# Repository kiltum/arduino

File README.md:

# Arduino shield for automation purposes

ATTN: This is picture of very old board. I havent new pictures

What this shield can do?
- Work with any Arduino Nano
- Work from 15-30 AC/DC. 
- Have 4x220v sensor
- Have 4x8A switch relay
- Have 0-10V output
- Have two RS-485
- 3 PT1000/pulled down analog input

## Pin-out for auduio

- D2,D3,D4 - TX,RX and RE/DE of 485
- D11, D12, D13 - for second 485
- D5 - PWM output for 0-10V
- D6 - PWM output for second 0-10V
- D7-D10 - control for switch relay 1-4
- A4,A5,A6,A7 - pulled down input for PT1000
- A0-A3 - sensors input

## Pin-out for board

Take board like on picture

### Top. Left-to-right

- 1 - power in POSITIVE
- 2 - GND
- 3 - RS485B
- 4 - RS485A
- 5 - RS485B2
- 7 - RS485A2
- 6 - GND
- 8 - 5V
- 9 - A4

separator

- 10 - A5
- 11 - A6 
- 12 - A7
- 13 - 0-10V output 2
- 14 - 0-10V output 1
- 15 - GND
- 16 - R4 closed
- 17 - R4 open	
- 18 - R4 ground

### Bottom, left to right

- 1 - Sensor 1 220V / 24V Positive
- 2 - Sensor 1
- 3 - Sensor 2 220v / 24V Positive
- 4 - Sensor 2
- 5 - Sensor 3 220v / 24V Positive
- 6 - Sensor 3
- 7 - Sensor 4 220v / 24V Positive
- 8 - Sensor 4
- 9 - not connected

separator

- 10 - R1 ground
- 11 - R1 closed
- 12 - R1 open
- 13 - R2 ground 
- 14 - R2 closed
- 15 - R2 open
- 16 - R3 ground
- 17 - R3 close
- 18 - R3 open

## License

Do what you want. I do not rely for anything you do.

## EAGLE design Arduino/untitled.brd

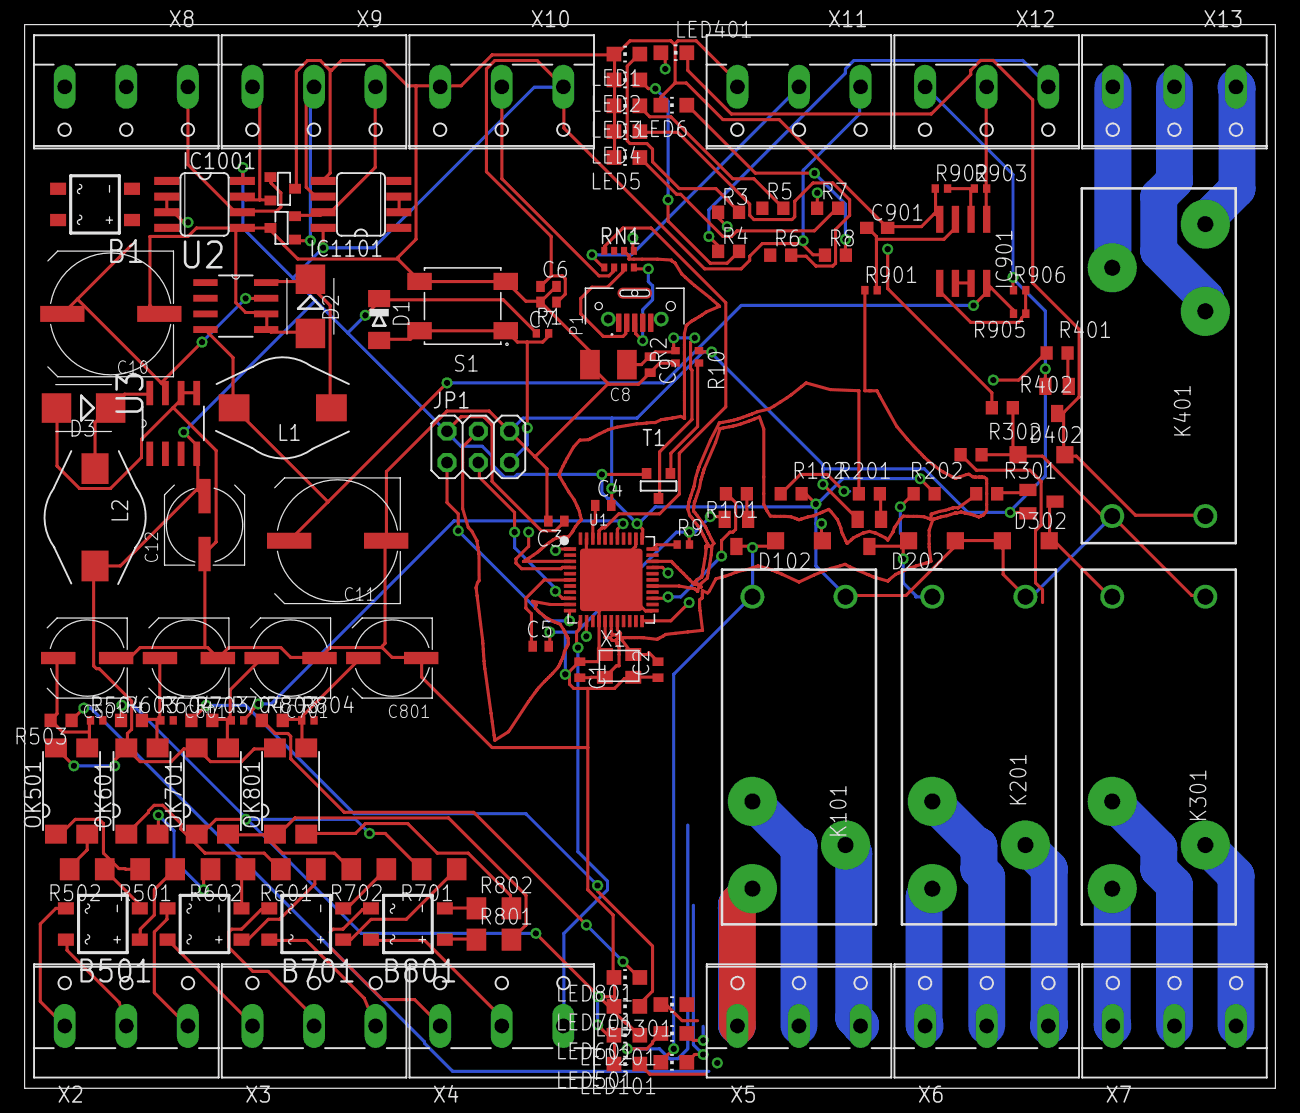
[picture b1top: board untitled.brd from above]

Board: 4 copper layers, 101.5 x 86.3 mm, 122 parts (0 on the bottom side), 118 nets.

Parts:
B1, B501, B601, B701, B801: B6S; MBS
C1, C2: 22pF; C0402
C3, C5: 1uF; C0402
C4, C6, C7, C9: 100n; C0402
C8: 22u; SMC_B
C10, C11: 220uFx35V; UD-10X10_NICHICON
C12: 220uFx10; UD-6,3X5,8_NICHICON
C501, C601, C701, C801: 100uFx6,3; UD-6,3X5,8_NICHICON
C901: 0.1uF; C0603
D1: CD1206-S01575; MINIMELF
D2, D3: MBRS130LT3; SMB
D102, D202, D302, D402: MBR0520LT; SOD123
D1001, D1101: CDSOT23-SM712; SOT-23-3
IC901: LM2904; SO08
IC1001, IC1101: MAX481CSA; SO08
JP1: 3x2M; 2X03
K101, K201, K301, K401: RT174005; RT-C/O12A3.5
L1: DO3308P-334MLD; BOURNS_SRR0805
L2: DO3316-224; BOURNS_SRR0805
LED1, LED2, LED3, LED4, LED5, LED6, LED101, LED201, LED301, LED401, LED501, LED601, LED701, LED801: IN-S85AT5B; CHIP-LED0805
OK501, OK601, OK701, OK801: LTV816S; SMD4
P1: KMMVX-SMT-BS-BTR; KYCON_KMMVX-SMT-BS-BTR
Q101, Q201, Q301, Q401: BSS138L
R1, R2, R9, R10, R504, R604, R704, R804: 10K; R0402
R3, R4, R5, R6, R7, R8, R102, R202, R302, R402, R503, R603, R703, R803: 600; R0603
R101, R201, R301, R401: 1K; R0603
R501, R502, R601, R602, R701, R702, R801, R802: 82K; R1206
R901: 10k; R0402
R902, R903, R905, R906: 4.7k; R0402
RN1: 22R; CAY16
S1: 430481035816_430481035816; 430481035816
T1: FDN340P/PMV48XP; SOT-23
U1: MCU-ATMEGA32U4-MUR(VQFN44); QFN44G-0.5-7X7MM
U2: LM2594M-12; SOIC127P620X175-8N
U3: LM2594M-05; SOIC127P620X175-8N
X1: 16MHz KX-7; CRYSTAL-3.2-2.5
X2, X3, X4, X5, X6, X7, X8, X9, X10, X11, X12, X13: W237-103

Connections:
0-10V1:N$1: IC901.5, R905.1, R906.2
0-10V1:N$2: C901.1, IC901.3, R901.2
0-10V1:N$3: IC901.6, IC901.7
0-10V1:N$4: IC901.2, R902.2, R903.1
10V1: IC901.1, R903.2, X12.2
24V1: B1.AC1, X8.3
24V2: B1.AC2, X8.2
+5V: C3.1, C6.1, C7.1, C12.+, D1.C, D102.C, D202.C, D302.C, D402.C, IC1001.8, IC1101.8, JP1.2, K101.A2, K201.A2, K301.A2, K401.A2, L2.2, OK501.4, OK601.4, OK701.4, OK801.4, R1.1, R8.1, R102.2, R202.2, R302.2, R402.2, T1.2, U1.2, U1.14, U1.24, U1.34, U1.44, U3.4, X10.1, X11.1
+12V: C11.+, IC901.8, L1.2, R905.2, U2.4
A0/S1: R504.2, U1.36
A1/S2: R604.2, U1.37
A2/S3: R704.2, U1.38
A3/S4: R804.2, U1.39
A4: RN1.3, U1.40
A4O: RN1.6, X10.2
A5: RN1.4, U1.41
A5O: RN1.5, X11.2
AREF: C4.1, U1.42
D0/RX/RS485R2: IC1101.1, U1.20
D1/TX/RS485D2: IC1101.4, U1.21
D2/SDA/RS485REDE2: IC1101.2, IC1101.3, U1.19
D3/SCL/PWM: R901.1, U1.18
D4/R1: R101.1, U1.25
D5/R2: R201.1, U1.31
D6/R3: R301.1, U1.27
D7/R4: R401.1, U1.1
D+: P1.3, RN1.8
D-: P1.2, RN1.7
GND: B1.-, C1.1, C2.1, C3.2, C4.2, C5.2, C6.2, C7.2, C8.-, C9.2, C10.-, C11.-, C12.-, C501.-, C601.-, C701.-, C801.-, C901.2, D2.A, D3.A, D1001.3, D1101.3, IC901.4, IC1001.5, IC1101.5, JP1.6, LED1.C, LED2.C, LED3.C, LED4.C, LED5.C, LED6.C, LED501.C, LED601.C, LED701.C, LED801.C, P1.5, Q101.S, Q201.S, Q301.S, Q401.S, R2.1, R9.2, R10.1, R902.1, R906.1, S1.3, S1.4, U1.5, U1.15, U1.23, U1.35, U1.43, U1.TAB, U2.5, U2.6, U3.5, U3.6, X1.2, X1.4, X10.3, X11.3, X12.3
HWB: R9.1, U1.33
IO8/RS485R1: IC1001.1, U1.28
IO9/RS485D1: IC1001.4, U1.29
IO10/RS485REDE1: IC1001.2, IC1001.3, U1.30
IO11: R3.1, U1.12, X4.3
IO12: R4.1, U1.26, X12.1
IO13: R5.1, U1.32
MISO: JP1.1, U1.11
MOSI: JP1.4, U1.10
unnamed: B1.+, C10.+, U2.7, U3.7
unnamed: D2.C, L1.1, U2.8
unnamed: LED3.A, R5.2
unnamed: LED4.A, R6.2
unnamed: LED5.A, R7.2
unnamed: D3.C, L2.1, U3.8
unnamed: LED6.A, R8.2
unnamed: R10.2, T1.3
unnamed: LED2.A, R4.2
unnamed: LED1.A, R3.2
R1G: K101.11, X5.3
R1NC: K101.12, X5.2
R1NO: K101.14, X5.1
R2G: K201.11, X6.3
R2NC: K201.12, X6.2
R2NO: K201.14, X6.1
R3G: K301.11, X7.3
R3NC: K301.12, X7.2
R3NO: K301.14, X7.1
R4G: K401.11, X13.3
R4NC: K401.12, X13.2
R4NO: K401.14, X13.1
RD+: RN1.1, U1.4
RD-: RN1.2, U1.3
RELAY1:N$1: D102.A, K101.A1, LED101.C, Q101.D
RELAY1:N$2: LED101.A, R102.1
RELAY1:N$4: Q101.G, R101.2
RELAY2:N$1: D202.A, K201.A1, LED201.C, Q201.D
RELAY2:N$2: LED201.A, R202.1
RELAY2:N$4: Q201.G, R201.2
RELAY3:N$1: D302.A, K301.A1, LED301.C, Q301.D
RELAY3:N$2: LED301.A, R302.1
RELAY3:N$4: Q301.G, R301.2
RELAY4:N$1: D402.A, K401.A1, LED401.C, Q401.D
RELAY4:N$2: LED401.A, R402.1
RELAY4:N$4: Q401.G, R401.2
RESET: D1.A, JP1.5, R1.2, S1.1, S1.2, U1.13
RS485A1: D1001.2, IC1001.7, X9.3
RS485A2: D1101.2, IC1101.7, X9.1
RS485B1: D1001.1, IC1001.6, X8.1
RS485B2: D1101.1, IC1101.6, X9.2
RXLED/SS: R6.1, U1.8
S11: B501.AC1, X2.2
S12: B501.AC2, X2.1
S21: B601.AC1, X3.1
S22: B601.AC2, X2.3
S31: B701.AC1, X3.3
S32: B701.AC2, X3.2
S41: B801.AC1, X4.2
S42: B801.AC2, X4.1
SCK: JP1.3, U1.9
SENSE1:N$2: LED501.A, R503.1
SENSE1:N$3: B501.+, R501.1
SENSE1:N$4: OK501.1, R501.2
SENSE1:N$5: OK501.2, R502.2
SENSE1:N$6: B501.-, R502.1
SENSE1:N$10: C501.+, OK501.3, R503.2, R504.1
SENSE2:N$2: LED601.A, R603.1
SENSE2:N$3: B601.+, R601.1
SENSE2:N$4: OK601.1, R601.2
SENSE2:N$5: OK601.2, R602.2
SENSE2:N$6: B601.-, R602.1
SENSE2:N$10: C601.+, OK601.3, R603.2, R604.1
SENSE3:N$2: LED701.A, R703.1
SENSE3:N$3: B701.+, R701.1
SENSE3:N$4: OK701.1, R701.2
SENSE3:N$5: OK701.2, R702.2
SENSE3:N$6: B701.-, R702.1
SENSE3:N$10: C701.+, OK701.3, R703.2, R704.1
SENSE4:N$2: LED801.A, R803.1
SENSE4:N$3: B801.+, R801.1
SENSE4:N$4: OK801.1, R801.2
SENSE4:N$5: OK801.2, R802.2
SENSE4:N$6: B801.-, R802.1
SENSE4:N$10: C801.+, OK801.3, R803.2, R804.1
TXLED: R7.1, U1.22
UCAP: C5.1, U1.6
VUSB: C8.+, C9.1, P1.1, R2.2, T1.1, U1.7
XTAL1: C2.2, U1.17, X1.3
XTAL2: C1.2, U1.16, X1.1

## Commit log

2017-03-04 :boom::camel: Added .gitattributes & .gitignore files
2017-03-04 First page
2017-03-04 power done
2017-03-04 Almost done
2017-03-04 Electrical done
2017-03-04 First success route
2017-03-04 NICE
2017-03-04 All done, but need nice touches like labeling
2017-03-04 Awesome
2017-03-04 add nice pic
2017-03-05 fix stupid error
2017-03-05 new 3d model
2017-03-05 add readme
2017-03-05 forget to out DQ
2017-03-05 new description
2017-03-05 updated bom
2017-03-05 updated schem file
2017-03-07 New version. Now inputs can handle 24V too
2017-03-07 numbers
2017-03-07 new 3d
2017-03-15 New PWM values & board
2017-03-27 another version
2017-03-27 4 layer!
2017-03-27 stm part
2017-04-01 Remove unneccessary
2017-04-02 New version, better (i hope)
2017-04-02 new picture
2017-04-02 chnage
2017-04-05 small changes for stability
2017-04-05 one more
2017-04-09 New gerber & bom
2017-04-26 ready to prod
2017-05-19 ready
2017-06-30 Clean up from oldies
2017-06-30 new power
2017-06-30 add calc
2017-07-09 New version
    Chnage power scheme
2017-07-09 add bom
2017-07-10 one more version
2017-07-10 Final
2017-07-12 pinout
2017-07-13 add universal
2017-07-25 Latsest assy
2019-01-20 ne scheme from eagle
2019-01-27 schem look done
2019-01-27 first try:
2019-02-10 12V part redesign
2019-02-10 first step on chem done
2019-02-10 first build
2019-02-17 last
2019-02-23 gogog
2019-02-23 gerber
2019-02-23 remove old
2019-02-23 try to use pcbway
2019-02-23 shematics upload
2019-02-24 move to old gerber
2020-10-25 rewrite
2020-10-25 loks like final
2020-10-25 looks like final
2020-11-28 rewrite schematics for jclpcb
2020-11-28 Return two -10V
2020-11-28 remove diodes
2020-11-28 near final
2020-11-28 test
2020-11-28 ready for route?
2020-11-28 try to send to jclpcb
2020-11-28 try to upload to jclpcb
2020-11-28 next try
2020-11-28 llok
2020-11-28 remove trash
